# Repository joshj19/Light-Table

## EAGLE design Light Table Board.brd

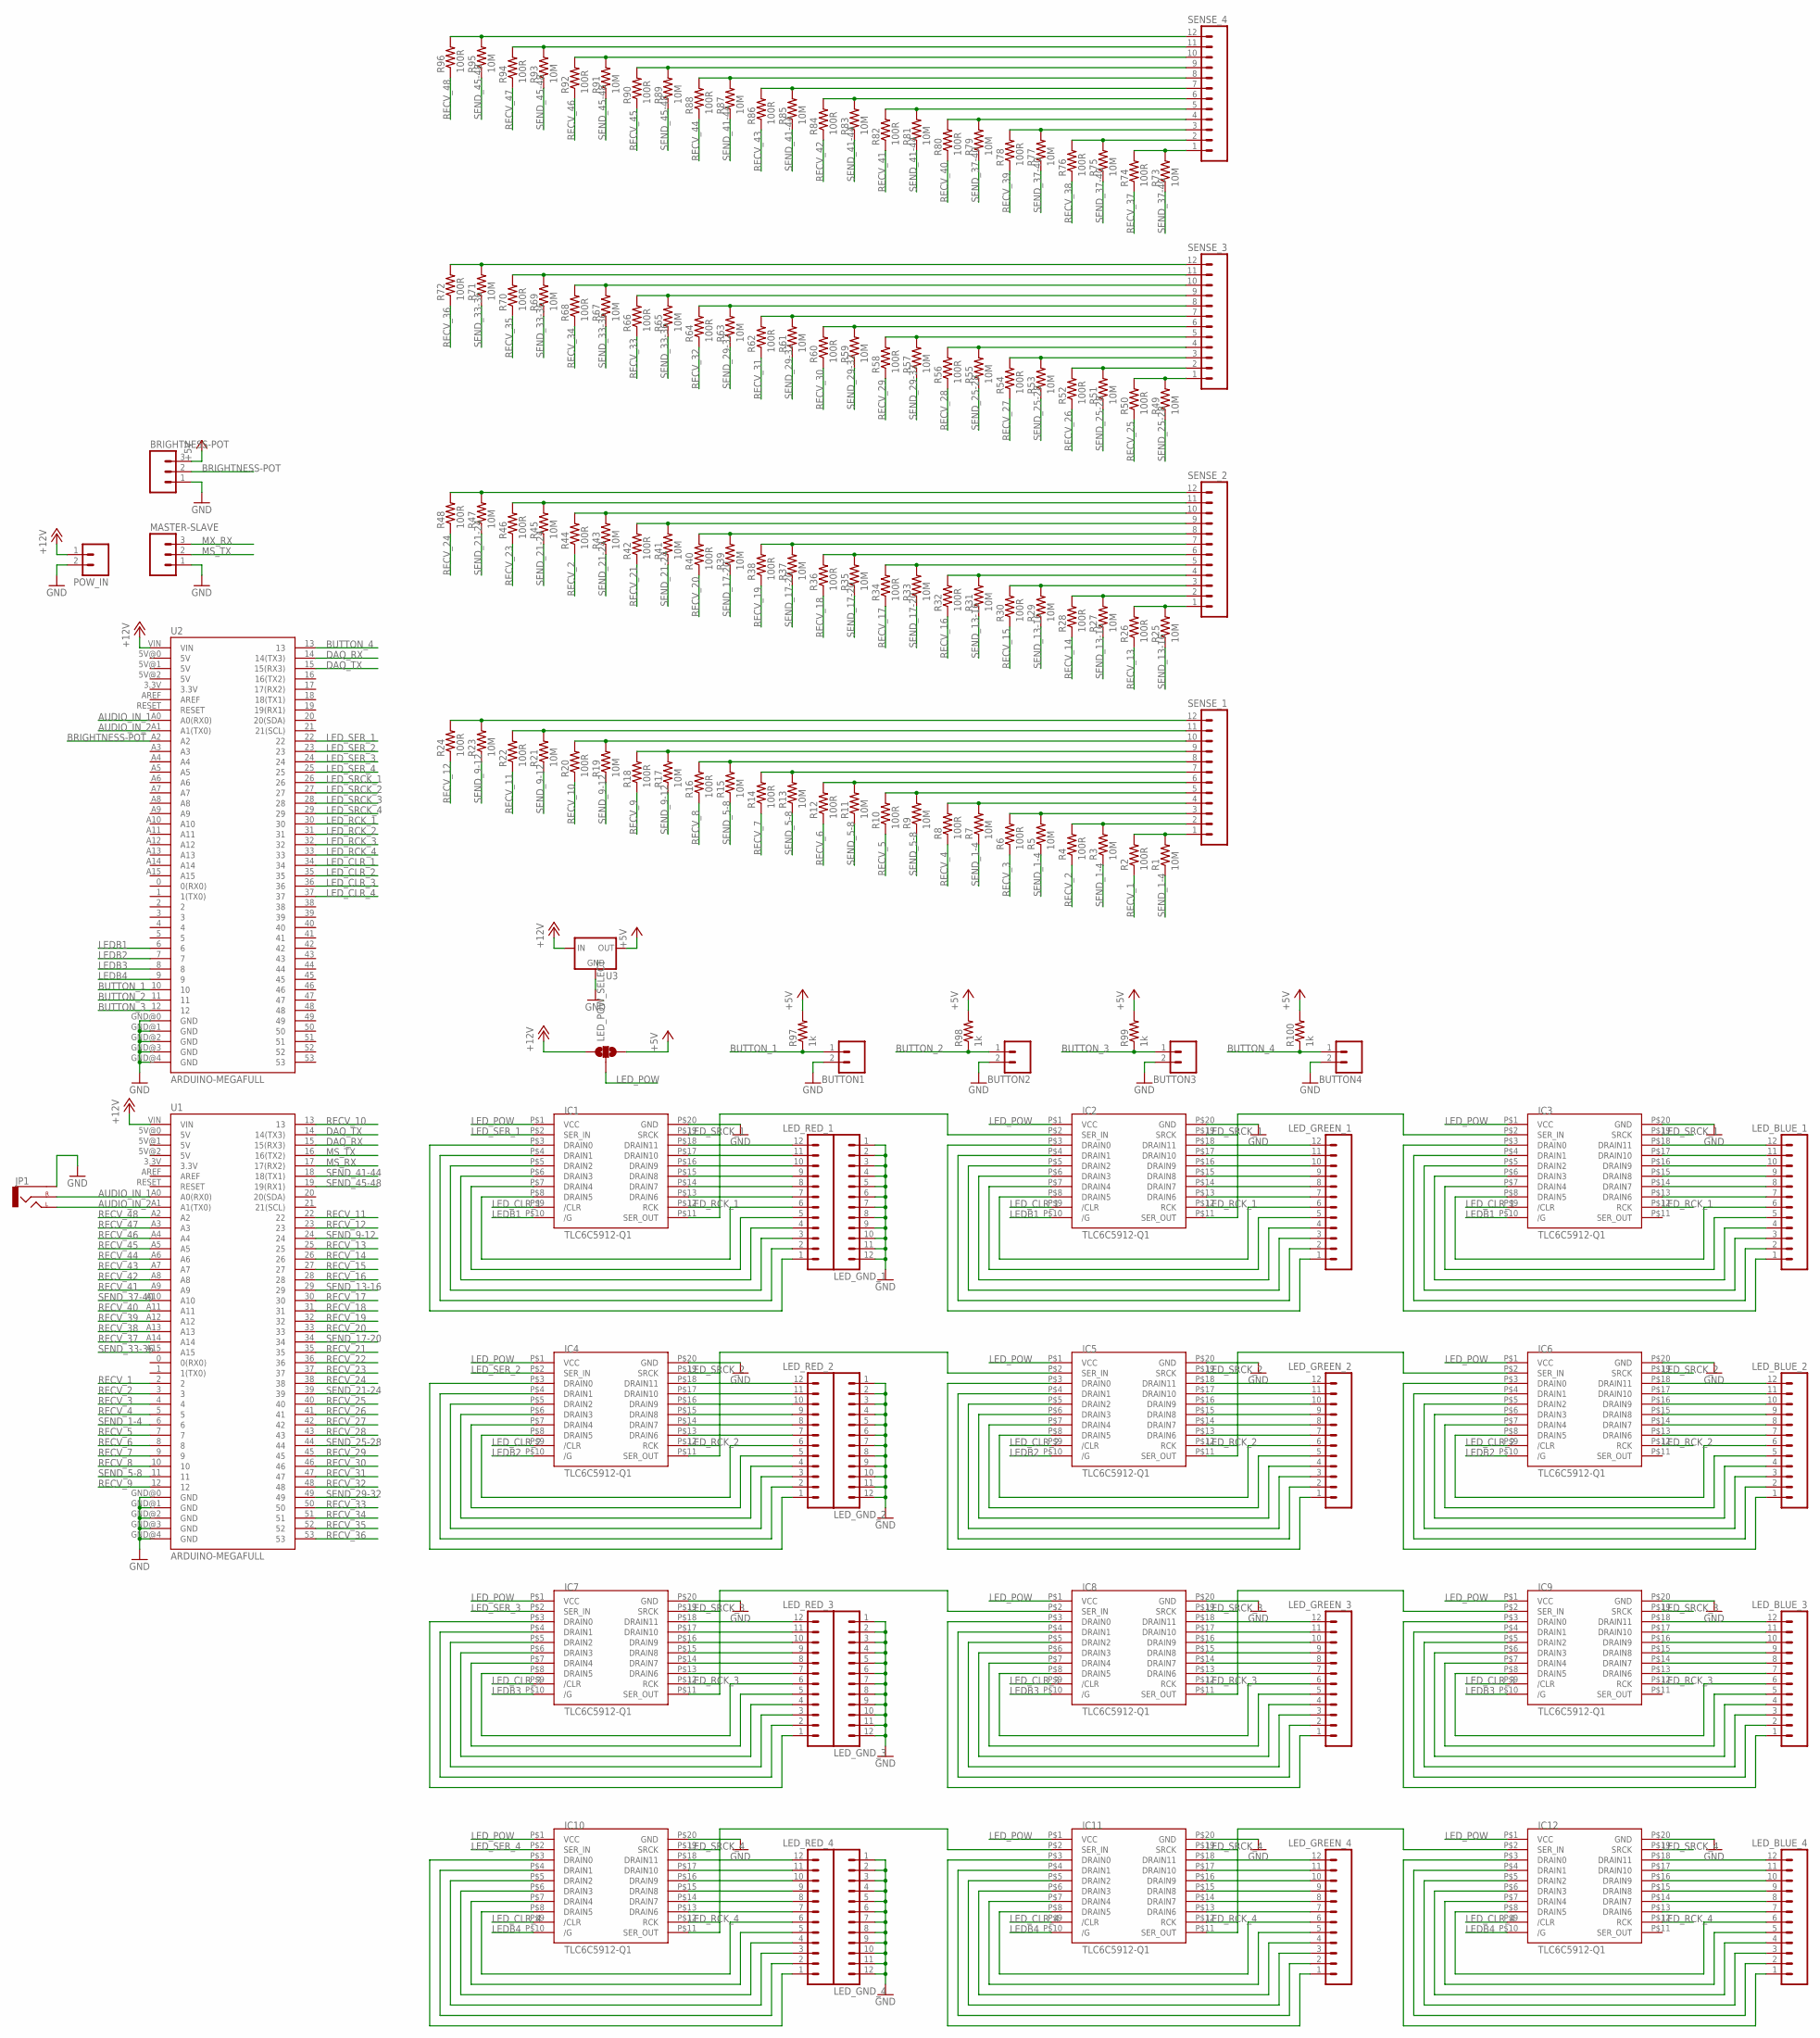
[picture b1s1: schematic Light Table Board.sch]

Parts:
BRIGHTNESS-POT: M03SCREW; SCREWTERMINAL-3.5MM-3
BUTTON1, BUTTON2, BUTTON3, BUTTON4: M023.5MM-NO_SILK; SCREWTERMINAL-3.5MM-2-NS
IC1, IC2, IC3, IC4, IC5, IC6, IC7, IC8, IC9, IC10, IC11, IC12: TLC6C5912-Q1; SOIC-20
JP1: AUDIO-JACK2.5MM; STEREOJACK2.5MM_STEREOJACK2.5MM
LED_BLUE_1, LED_BLUE_2, LED_BLUE_3, LED_BLUE_4: M12LONGPADS; 1X12_LONGPADS
LED_GND_1, LED_GND_2, LED_GND_3, LED_GND_4: M12LONGPADS; 1X12_LONGPADS
LED_GREEN_1, LED_GREEN_2, LED_GREEN_3, LED_GREEN_4: M12LONGPADS; 1X12_LONGPADS
LED_POW_SELECT: SOLDERJUMPER_2WAYS; SJ_3
LED_RED_1, LED_RED_2, LED_RED_3, LED_RED_4: M12LONGPADS; 1X12_LONGPADS
MASTER-SLAVE: M03SCREW; SCREWTERMINAL-3.5MM-3
POW_IN: M023.5MM-NO_SILK; SCREWTERMINAL-3.5MM-2-NS
R1, R3, R5, R7, R9, R11, R13, R15, R17, R19, R21, R23, R25, R27, R29, R31, R33, R35, R37, R39, R41, R43, R45, R47, R49, R51, R53, R55, R57, R59, R61, R63, R65, R67, R69, R71, R73, R75, R77, R79, R81, R83, R85, R87, R89, R91, R93, R95: 10M; R1206
R2, R4, R6, R8, R10, R12, R14, R16, R18, R20, R22, R24, R26, R28, R30, R32, R34, R36, R38, R40, R42, R44, R46, R48, R50, R52, R54, R56, R58, R60, R62, R64, R66, R68, R70, R72, R74, R76, R78, R80, R82, R84, R86, R88, R90, R92, R94, R96: 100R; R1206
R97, R98, R99, R100: 1k; R1206
SENSE_1, SENSE_2, SENSE_3, SENSE_4: M12LONGPADS; 1X12_LONGPADS
U1, U2: ARDUINO-MEGAFULL; ARDUINO_MEGA
U3: V_REG_78XX-TO-220; TO-220-ALT

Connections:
+5V: BRIGHTNESS-POT.3, LED_POW_SELECT.3, R97.2, R98.2, R99.2, R100.2, U3.OUT
+12V: LED_POW_SELECT.1, POW_IN.1, U1.VIN, U2.VIN, U3.IN
AUDIO_IN_1: JP1.TIP (RIGHT), U1.A0 (A0(RX0)), U2.A0 (A0(RX0))
AUDIO_IN_2: JP1.SHIELD (LEFT), U1.A1 (A1(TX0)), U2.A1 (A1(TX0))
BRIGHTNESS-POT: BRIGHTNESS-POT.2, U2.A2
BUTTON_1: BUTTON1.1, R97.1, U2.10
BUTTON_2: BUTTON2.1, R98.1, U2.11
BUTTON_3: BUTTON3.1, R99.1, U2.12
BUTTON_4: BUTTON4.1, R100.1, U2.13
DAQ_RX: U1.15 (15(RX3)), U2.14 (14(TX3))
DAQ_TX: U1.14 (14(TX3)), U2.15 (15(RX3))
GND: BRIGHTNESS-POT.1, BUTTON1.2, BUTTON2.2, BUTTON3.2, BUTTON4.2, IC1.P$20 (GND), IC2.P$20 (GND), IC3.P$20 (GND), IC4.P$20 (GND), IC5.P$20 (GND), IC6.P$20 (GND), IC7.P$20 (GND), IC8.P$20 (GND), IC9.P$20 (GND), IC10.P$20 (GND), IC11.P$20 (GND), IC12.P$20 (GND), JP1.RING1 (SLEEVE), LED_GND_1.1, LED_GND_1.2, LED_GND_1.3, LED_GND_1.4, LED_GND_1.5, LED_GND_1.6, LED_GND_1.7, LED_GND_1.8, LED_GND_1.9, LED_GND_1.10, LED_GND_1.11, LED_GND_1.12, LED_GND_2.1, LED_GND_2.2, LED_GND_2.3, LED_GND_2.4, LED_GND_2.5, LED_GND_2.6, LED_GND_2.7, LED_GND_2.8, LED_GND_2.9, LED_GND_2.10, LED_GND_2.11, LED_GND_2.12, LED_GND_3.1, LED_GND_3.2, LED_GND_3.3, LED_GND_3.4, LED_GND_3.5, LED_GND_3.6, LED_GND_3.7, LED_GND_3.8, LED_GND_3.9, LED_GND_3.10, LED_GND_3.11, LED_GND_3.12, LED_GND_4.1, LED_GND_4.2, LED_GND_4.3, LED_GND_4.4, LED_GND_4.5, LED_GND_4.6, LED_GND_4.7, LED_GND_4.8, LED_GND_4.9, LED_GND_4.10, LED_GND_4.11, LED_GND_4.12, MASTER-SLAVE.1, POW_IN.2, U1.GND@0 (GND), U1.GND@1 (GND), U1.GND@2 (GND), U1.GND@3 (GND), U1.GND@4 (GND), U2.GND@0 (GND), U2.GND@1 (GND), U2.GND@2 (GND), U2.GND@3 (GND), U2.GND@4 (GND), U3.GND
LEDB1: IC1.P$10 (/G), IC2.P$10 (/G), IC3.P$10 (/G), U2.6
LEDB2: IC4.P$10 (/G), IC5.P$10 (/G), IC6.P$10 (/G), U2.7
LEDB3: IC7.P$10 (/G), IC8.P$10 (/G), IC9.P$10 (/G), U2.8
LEDB4: IC10.P$10 (/G), IC11.P$10 (/G), IC12.P$10 (/G), U2.9
LED_CLR_1: IC1.P$9 (/CLR), IC2.P$9 (/CLR), IC3.P$9 (/CLR), U2.34
LED_CLR_2: IC4.P$9 (/CLR), IC5.P$9 (/CLR), IC6.P$9 (/CLR), U2.35
LED_CLR_3: IC7.P$9 (/CLR), IC8.P$9 (/CLR), IC9.P$9 (/CLR), U2.36
LED_CLR_4: IC10.P$9 (/CLR), IC11.P$9 (/CLR), IC12.P$9 (/CLR), U2.37
LED_POW: IC1.P$1 (VCC), IC2.P$1 (VCC), IC3.P$1 (VCC), IC4.P$1 (VCC), IC5.P$1 (VCC), IC6.P$1 (VCC), IC7.P$1 (VCC), IC8.P$1 (VCC), IC9.P$1 (VCC), IC10.P$1 (VCC), IC11.P$1 (VCC), IC12.P$1 (VCC), LED_POW_SELECT.2
LED_RCK_1: IC1.P$12 (RCK), IC2.P$12 (RCK), IC3.P$12 (RCK), U2.30
LED_RCK_2: IC4.P$12 (RCK), IC5.P$12 (RCK), IC6.P$12 (RCK), U2.31
LED_RCK_3: IC7.P$12 (RCK), IC8.P$12 (RCK), IC9.P$12 (RCK), U2.32
LED_RCK_4: IC10.P$12 (RCK), IC11.P$12 (RCK), IC12.P$12 (RCK), U2.33
LED_SER_1: IC1.P$2 (SER_IN), U2.22
LED_SER_2: IC4.P$2 (SER_IN), U2.23
LED_SER_3: IC7.P$2 (SER_IN), U2.24
LED_SER_4: IC10.P$2 (SER_IN), U2.25
LED_SRCK_1: IC1.P$19 (SRCK), IC2.P$19 (SRCK), IC3.P$19 (SRCK), U2.26
LED_SRCK_2: IC4.P$19 (SRCK), IC5.P$19 (SRCK), IC6.P$19 (SRCK), U2.27
LED_SRCK_3: IC7.P$19 (SRCK), IC8.P$19 (SRCK), IC9.P$19 (SRCK), U2.28
LED_SRCK_4: IC10.P$19 (SRCK), IC11.P$19 (SRCK), IC12.P$19 (SRCK), U2.29
MS_RX: U1.17 (17(RX2))
MS_TX: MASTER-SLAVE.2, U1.16 (16(TX2))
MX_RX: MASTER-SLAVE.3
unnamed: IC1.P$8 (DRAIN5), LED_RED_1.6
unnamed: IC1.P$18 (DRAIN11), LED_RED_1.12
unnamed: IC1.P$17 (DRAIN10), LED_RED_1.11
unnamed: IC1.P$16 (DRAIN9), LED_RED_1.10
unnamed: IC1.P$15 (DRAIN8), LED_RED_1.9
unnamed: IC1.P$14 (DRAIN7), LED_RED_1.8
unnamed: IC1.P$13 (DRAIN6), LED_RED_1.7
unnamed: IC1.P$7 (DRAIN4), LED_RED_1.5
unnamed: IC1.P$6 (DRAIN3), LED_RED_1.4
unnamed: IC1.P$5 (DRAIN2), LED_RED_1.3
unnamed: IC1.P$4 (DRAIN1), LED_RED_1.2
unnamed: IC1.P$3 (DRAIN0), LED_RED_1.1
unnamed: IC2.P$8 (DRAIN5), LED_GREEN_1.6
unnamed: IC2.P$18 (DRAIN11), LED_GREEN_1.12
unnamed: IC2.P$17 (DRAIN10), LED_GREEN_1.11
unnamed: IC2.P$16 (DRAIN9), LED_GREEN_1.10
unnamed: IC2.P$15 (DRAIN8), LED_GREEN_1.9
unnamed: IC2.P$14 (DRAIN7), LED_GREEN_1.8
unnamed: IC2.P$13 (DRAIN6), LED_GREEN_1.7
unnamed: IC2.P$7 (DRAIN4), LED_GREEN_1.5
unnamed: IC2.P$6 (DRAIN3), LED_GREEN_1.4
unnamed: IC2.P$5 (DRAIN2), LED_GREEN_1.3
unnamed: IC2.P$4 (DRAIN1), LED_GREEN_1.2
unnamed: IC2.P$3 (DRAIN0), LED_GREEN_1.1
unnamed: IC1.P$11 (SER_OUT), IC2.P$2 (SER_IN)
unnamed: IC3.P$8 (DRAIN5), LED_BLUE_1.6
unnamed: IC3.P$18 (DRAIN11), LED_BLUE_1.12
unnamed: IC3.P$17 (DRAIN10), LED_BLUE_1.11
unnamed: IC3.P$16 (DRAIN9), LED_BLUE_1.10
unnamed: IC3.P$15 (DRAIN8), LED_BLUE_1.9
unnamed: IC3.P$14 (DRAIN7), LED_BLUE_1.8
unnamed: IC3.P$13 (DRAIN6), LED_BLUE_1.7
unnamed: IC3.P$7 (DRAIN4), LED_BLUE_1.5
unnamed: IC3.P$6 (DRAIN3), LED_BLUE_1.4
unnamed: IC3.P$5 (DRAIN2), LED_BLUE_1.3
unnamed: IC3.P$4 (DRAIN1), LED_BLUE_1.2
unnamed: IC3.P$3 (DRAIN0), LED_BLUE_1.1
unnamed: IC2.P$11 (SER_OUT), IC3.P$2 (SER_IN)
unnamed: R1.2, R2.2, SENSE_1.1
unnamed: IC4.P$8 (DRAIN5), LED_RED_2.6
unnamed: IC4.P$18 (DRAIN11), LED_RED_2.12
unnamed: IC4.P$17 (DRAIN10), LED_RED_2.11
unnamed: IC4.P$16 (DRAIN9), LED_RED_2.10
unnamed: IC4.P$15 (DRAIN8), LED_RED_2.9
unnamed: IC4.P$14 (DRAIN7), LED_RED_2.8
unnamed: IC4.P$13 (DRAIN6), LED_RED_2.7
unnamed: IC4.P$7 (DRAIN4), LED_RED_2.5
unnamed: IC4.P$6 (DRAIN3), LED_RED_2.4
unnamed: IC4.P$5 (DRAIN2), LED_RED_2.3
unnamed: IC4.P$4 (DRAIN1), LED_RED_2.2
unnamed: IC4.P$3 (DRAIN0), LED_RED_2.1
unnamed: IC5.P$8 (DRAIN5), LED_GREEN_2.6
unnamed: IC5.P$18 (DRAIN11), LED_GREEN_2.12
unnamed: IC5.P$17 (DRAIN10), LED_GREEN_2.11
unnamed: IC5.P$16 (DRAIN9), LED_GREEN_2.10
unnamed: IC5.P$15 (DRAIN8), LED_GREEN_2.9
unnamed: IC5.P$14 (DRAIN7), LED_GREEN_2.8
unnamed: IC5.P$13 (DRAIN6), LED_GREEN_2.7
unnamed: IC5.P$7 (DRAIN4), LED_GREEN_2.5
unnamed: IC5.P$6 (DRAIN3), LED_GREEN_2.4
unnamed: IC5.P$5 (DRAIN2), LED_GREEN_2.3
unnamed: IC5.P$4 (DRAIN1), LED_GREEN_2.2
unnamed: IC5.P$3 (DRAIN0), LED_GREEN_2.1
unnamed: IC4.P$11 (SER_OUT), IC5.P$2 (SER_IN)
unnamed: IC6.P$8 (DRAIN5), LED_BLUE_2.6
unnamed: IC6.P$18 (DRAIN11), LED_BLUE_2.12
unnamed: IC6.P$17 (DRAIN10), LED_BLUE_2.11
unnamed: IC6.P$16 (DRAIN9), LED_BLUE_2.10
unnamed: IC6.P$15 (DRAIN8), LED_BLUE_2.9
unnamed: IC6.P$14 (DRAIN7), LED_BLUE_2.8
unnamed: IC6.P$13 (DRAIN6), LED_BLUE_2.7
unnamed: IC6.P$7 (DRAIN4), LED_BLUE_2.5
unnamed: IC6.P$6 (DRAIN3), LED_BLUE_2.4
unnamed: IC6.P$5 (DRAIN2), LED_BLUE_2.3
unnamed: IC6.P$4 (DRAIN1), LED_BLUE_2.2
unnamed: IC6.P$3 (DRAIN0), LED_BLUE_2.1
unnamed: IC5.P$11 (SER_OUT), IC6.P$2 (SER_IN)
unnamed: IC7.P$8 (DRAIN5), LED_RED_3.6
unnamed: IC7.P$18 (DRAIN11), LED_RED_3.12
unnamed: IC7.P$17 (DRAIN10), LED_RED_3.11
unnamed: IC7.P$16 (DRAIN9), LED_RED_3.10
unnamed: IC7.P$15 (DRAIN8), LED_RED_3.9
unnamed: IC7.P$14 (DRAIN7), LED_RED_3.8
unnamed: IC7.P$13 (DRAIN6), LED_RED_3.7
unnamed: IC7.P$7 (DRAIN4), LED_RED_3.5
unnamed: IC7.P$6 (DRAIN3), LED_RED_3.4
unnamed: IC7.P$5 (DRAIN2), LED_RED_3.3
unnamed: IC7.P$4 (DRAIN1), LED_RED_3.2
unnamed: IC7.P$3 (DRAIN0), LED_RED_3.1
unnamed: IC8.P$8 (DRAIN5), LED_GREEN_3.6
unnamed: IC8.P$18 (DRAIN11), LED_GREEN_3.12
unnamed: IC8.P$17 (DRAIN10), LED_GREEN_3.11
unnamed: IC8.P$16 (DRAIN9), LED_GREEN_3.10
unnamed: IC8.P$15 (DRAIN8), LED_GREEN_3.9
unnamed: IC8.P$14 (DRAIN7), LED_GREEN_3.8
unnamed: IC8.P$13 (DRAIN6), LED_GREEN_3.7
unnamed: IC8.P$7 (DRAIN4), LED_GREEN_3.5
unnamed: IC8.P$6 (DRAIN3), LED_GREEN_3.4
unnamed: IC8.P$5 (DRAIN2), LED_GREEN_3.3
unnamed: IC8.P$4 (DRAIN1), LED_GREEN_3.2
unnamed: IC8.P$3 (DRAIN0), LED_GREEN_3.1
unnamed: IC7.P$11 (SER_OUT), IC8.P$2 (SER_IN)
unnamed: IC9.P$8 (DRAIN5), LED_BLUE_3.6
unnamed: IC9.P$18 (DRAIN11), LED_BLUE_3.12
unnamed: IC9.P$17 (DRAIN10), LED_BLUE_3.11
unnamed: IC9.P$16 (DRAIN9), LED_BLUE_3.10
unnamed: IC9.P$15 (DRAIN8), LED_BLUE_3.9
unnamed: IC9.P$14 (DRAIN7), LED_BLUE_3.8
unnamed: IC9.P$13 (DRAIN6), LED_BLUE_3.7
unnamed: IC9.P$7 (DRAIN4), LED_BLUE_3.5
unnamed: IC9.P$6 (DRAIN3), LED_BLUE_3.4
unnamed: IC9.P$5 (DRAIN2), LED_BLUE_3.3
unnamed: IC9.P$4 (DRAIN1), LED_BLUE_3.2
unnamed: IC9.P$3 (DRAIN0), LED_BLUE_3.1
unnamed: IC8.P$11 (SER_OUT), IC9.P$2 (SER_IN)
unnamed: IC10.P$8 (DRAIN5), LED_RED_4.6
unnamed: IC10.P$18 (DRAIN11), LED_RED_4.12
unnamed: IC10.P$17 (DRAIN10), LED_RED_4.11
unnamed: IC10.P$16 (DRAIN9), LED_RED_4.10
unnamed: IC10.P$15 (DRAIN8), LED_RED_4.9
unnamed: IC10.P$14 (DRAIN7), LED_RED_4.8
unnamed: IC10.P$13 (DRAIN6), LED_RED_4.7
unnamed: IC10.P$7 (DRAIN4), LED_RED_4.5
unnamed: IC10.P$6 (DRAIN3), LED_RED_4.4
unnamed: IC10.P$5 (DRAIN2), LED_RED_4.3
unnamed: IC10.P$4 (DRAIN1), LED_RED_4.2
unnamed: IC10.P$3 (DRAIN0), LED_RED_4.1
unnamed: IC11.P$8 (DRAIN5), LED_GREEN_4.6
unnamed: IC11.P$18 (DRAIN11), LED_GREEN_4.12
unnamed: IC11.P$17 (DRAIN10), LED_GREEN_4.11
unnamed: IC11.P$16 (DRAIN9), LED_GREEN_4.10
unnamed: IC11.P$15 (DRAIN8), LED_GREEN_4.9
unnamed: IC11.P$14 (DRAIN7), LED_GREEN_4.8
unnamed: IC11.P$13 (DRAIN6), LED_GREEN_4.7
unnamed: IC11.P$7 (DRAIN4), LED_GREEN_4.5
unnamed: IC11.P$6 (DRAIN3), LED_GREEN_4.4
unnamed: IC11.P$5 (DRAIN2), LED_GREEN_4.3
unnamed: IC11.P$4 (DRAIN1), LED_GREEN_4.2
unnamed: IC11.P$3 (DRAIN0), LED_GREEN_4.1
unnamed: IC10.P$11 (SER_OUT), IC11.P$2 (SER_IN)
unnamed: IC12.P$8 (DRAIN5), LED_BLUE_4.6
unnamed: IC12.P$18 (DRAIN11), LED_BLUE_4.12
unnamed: IC12.P$17 (DRAIN10), LED_BLUE_4.11
unnamed: IC12.P$16 (DRAIN9), LED_BLUE_4.10
unnamed: IC12.P$15 (DRAIN8), LED_BLUE_4.9
unnamed: IC12.P$14 (DRAIN7), LED_BLUE_4.8
unnamed: IC12.P$13 (DRAIN6), LED_BLUE_4.7
unnamed: IC12.P$7 (DRAIN4), LED_BLUE_4.5
unnamed: IC12.P$6 (DRAIN3), LED_BLUE_4.4
unnamed: IC12.P$5 (DRAIN2), LED_BLUE_4.3
unnamed: IC12.P$4 (DRAIN1), LED_BLUE_4.2
unnamed: IC12.P$3 (DRAIN0), LED_BLUE_4.1
unnamed: IC11.P$11 (SER_OUT), IC12.P$2 (SER_IN)
unnamed: R3.2, R4.2, SENSE_1.2
unnamed: R5.2, R6.2, SENSE_1.3
unnamed: R7.2, R8.2, SENSE_1.4
unnamed: R9.2, R10.2, SENSE_1.5
unnamed: R11.2, R12.2, SENSE_1.6
unnamed: R13.2, R14.2, SENSE_1.7
unnamed: R15.2, R16.2, SENSE_1.8
unnamed: R17.2, R18.2, SENSE_1.9
unnamed: R19.2, R20.2, SENSE_1.10
unnamed: R21.2, R22.2, SENSE_1.11
unnamed: R23.2, R24.2, SENSE_1.12
unnamed: R25.2, R26.2, SENSE_2.1
unnamed: R27.2, R28.2, SENSE_2.2
unnamed: R29.2, R30.2, SENSE_2.3
unnamed: R31.2, R32.2, SENSE_2.4
unnamed: R33.2, R34.2, SENSE_2.5
unnamed: R35.2, R36.2, SENSE_2.6
unnamed: R37.2, R38.2, SENSE_2.7
unnamed: R39.2, R40.2, SENSE_2.8
unnamed: R41.2, R42.2, SENSE_2.9
unnamed: R43.2, R44.2, SENSE_2.10
unnamed: R45.2, R46.2, SENSE_2.11
unnamed: R47.2, R48.2, SENSE_2.12
unnamed: R49.2, R50.2, SENSE_3.1
unnamed: R51.2, R52.2, SENSE_3.2
unnamed: R53.2, R54.2, SENSE_3.3
unnamed: R55.2, R56.2, SENSE_3.4
unnamed: R57.2, R58.2, SENSE_3.5
unnamed: R59.2, R60.2, SENSE_3.6
unnamed: R61.2, R62.2, SENSE_3.7
unnamed: R63.2, R64.2, SENSE_3.8
unnamed: R65.2, R66.2, SENSE_3.9
unnamed: R67.2, R68.2, SENSE_3.10
unnamed: R69.2, R70.2, SENSE_3.11
unnamed: R71.2, R72.2, SENSE_3.12
unnamed: R73.2, R74.2, SENSE_4.1
unnamed: R75.2, R76.2, SENSE_4.2
unnamed: R77.2, R78.2, SENSE_4.3
unnamed: R79.2, R80.2, SENSE_4.4
unnamed: R81.2, R82.2, SENSE_4.5
unnamed: R83.2, R84.2, SENSE_4.6
unnamed: R85.2, R86.2, SENSE_4.7
unnamed: R87.2, R88.2, SENSE_4.8
unnamed: R89.2, R90.2, SENSE_4.9
unnamed: R91.2, R92.2, SENSE_4.10
unnamed: R93.2, R94.2, SENSE_4.11
unnamed: R95.2, R96.2, SENSE_4.12
RECV_1: R2.1, U1.2
RECV_2: R4.1, R44.1, U1.3
RECV_3: R6.1, U1.4
RECV_4: R8.1, U1.5
RECV_5: R10.1, U1.7
RECV_6: R12.1, U1.8
RECV_7: R14.1, U1.9
RECV_8: R16.1, U1.10
RECV_9: R18.1, U1.12
RECV_10: R20.1, U1.13
RECV_11: R22.1, U1.22
RECV_12: R24.1, U1.23
RECV_13: R26.1, U1.25
RECV_14: R28.1, U1.26
RECV_15: R30.1, U1.27
RECV_16: R32.1, U1.28
RECV_17: R34.1, U1.30
RECV_18: R36.1, U1.31
RECV_19: R38.1, U1.32
RECV_20: R40.1, U1.33
RECV_21: R42.1, U1.35
RECV_22: U1.36
RECV_23: R46.1, U1.37
RECV_24: R48.1, U1.38
RECV_25: R50.1, U1.40
RECV_26: R52.1, U1.41
RECV_27: R54.1, U1.42
RECV_28: R56.1, U1.43
RECV_29: R58.1, U1.45
RECV_30: R60.1, U1.46
RECV_31: R62.1, U1.47
RECV_32: R64.1, U1.48
RECV_33: R66.1, U1.50
RECV_34: R68.1, U1.51
RECV_35: R70.1, U1.52
RECV_36: R72.1, U1.53
RECV_37: R74.1, U1.A14
RECV_38: R76.1, U1.A13
RECV_39: R78.1, U1.A12
RECV_40: R80.1, U1.A11
RECV_41: R82.1, U1.A9
RECV_42: R84.1, U1.A8
RECV_43: R86.1, U1.A7
RECV_44: R88.1, U1.A6
RECV_45: R90.1, U1.A5
RECV_46: R92.1, U1.A4
RECV_47: R94.1, U1.A3
RECV_48: R96.1, U1.A2
SEND_1-4: R1.1, R3.1, R5.1, R7.1, U1.6
SEND_5-8: R9.1, R11.1, R13.1, R15.1, U1.11
SEND_9-12: R17.1, R19.1, R21.1, R23.1, U1.24
SEND_13-16: R25.1, R27.1, R29.1, R31.1, U1.29
SEND_17-20: R33.1, R35.1, R37.1, R39.1, U1.34
SEND_21-24: R41.1, R43.1, R45.1, R47.1, U1.39
SEND_25-28: R49.1, R51.1, R53.1, R55.1, U1.44
SEND_29-32: R57.1, R59.1, R61.1, R63.1, U1.49
SEND_33-36: R65.1, R67.1, R69.1, R71.1, U1.A15
SEND_37-40: R73.1, R75.1, R77.1, R79.1, U1.A10
SEND_41-44: R81.1, R83.1, R85.1, R87.1, U1.18 (18(TX1))
SEND_45-48: R89.1, R91.1, R93.1, R95.1, U1.19 (19(RX1))

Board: 2 copper layers, 144 parts (0 on the bottom side), 293 nets, no tracks yet.

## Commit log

2015-08-18 Actual first schematic design

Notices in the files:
parts and their libraries:
SparkFun-Connectors: Licensing: Creative Commons ShareAlike 4.0 International - https://creativecommons.org/licenses/by-sa/4.0
